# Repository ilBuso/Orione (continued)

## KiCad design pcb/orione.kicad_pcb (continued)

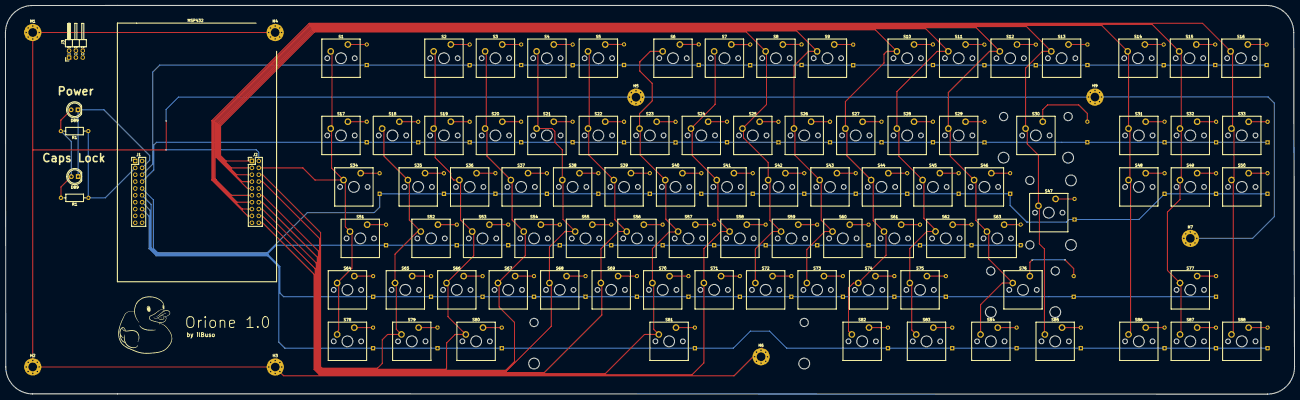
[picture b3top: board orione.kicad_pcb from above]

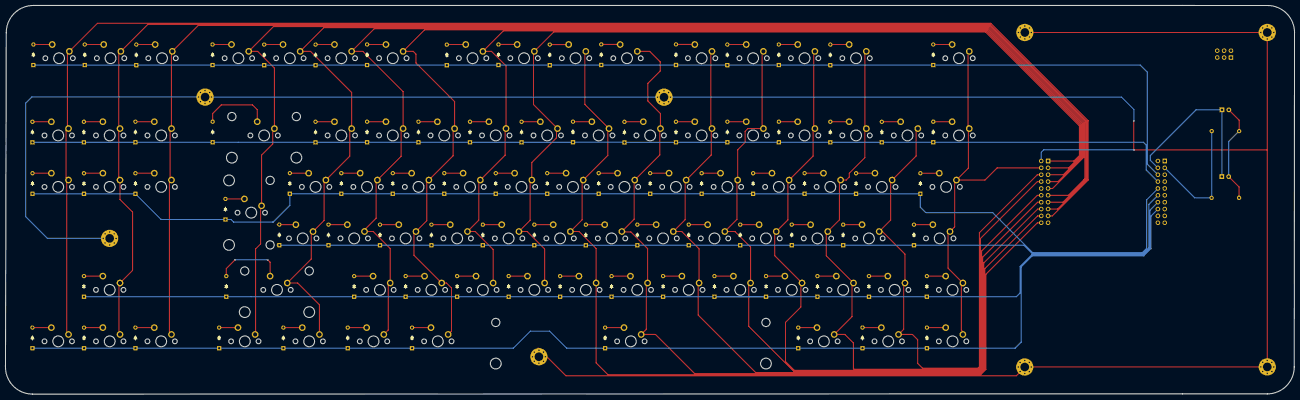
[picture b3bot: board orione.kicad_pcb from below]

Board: 2 copper layers, 477.1 x 143.8 mm, 191 parts (88 on the bottom side), 115 nets.

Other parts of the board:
D89#2: LED; LED_D5.0mm
R1#2: Resistor; R_Axial_DIN0207_L6.3mm_D2.5mm_P10.16mm_Horizontal

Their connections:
GND 1: D89#2.1 (K); also elsewhere on the board
Led 1: R1#2.1; also elsewhere on the board
unnamed 108: D89#2.2 (A), R1#2.2; also elsewhere on the board

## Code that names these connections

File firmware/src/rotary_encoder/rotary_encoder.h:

/**
 * @file rotary_encoder.h
 * @brief Rotary encoder definitions and state structure
 * 
 * Pin definitions, debounce timing constants, and state structure for
 * KY-040 rotary encoder module with integrated push button.
 */

#ifndef ROTARY_ENCODER_H
#define ROTARY_ENCODER_H

    #include <stdint.h>
    #include <stdbool.h>
    
    #include "pico/stdlib.h"
    #include "hardware/sync.h"
    
    #define ROTARY_CLK 19    // CLK pin (A)
    #define ROTARY_DT 20     // DT pin (B)
    #define ROTARY_SW 21     // Switch pin (button)

    // Rotary encoder state
    typedef struct {
        volatile int8_t direction;     // -1 for CCW, 1 for CW, 0 for no change
        volatile bool button_pressed;   // true when button is pressed
        volatile bool has_event;        // true when there's a new event to process
    } rotary_encoder_state_t;

    extern uint32_t last_encoder_time;
    extern uint32_t last_button_time;
    extern uint8_t last_clk_state;
    extern rotary_encoder_state_t rotary_state;

    // Get current state (call from main loop)
    void rotary_encoder_get_state(int8_t* direction, bool* button_pressed);

#endif /* ROTARY_ENCODER_H */

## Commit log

2024-12-30 Updated .gitignore
2024-12-30 Added version 1.0 of the pcb
2024-12-31 minor updtaes to pcb
2024-12-31 Updated MATERIALS.md
2025-01-01 TODO.md
2025-01-02 new usb
2025-01-02 pcv v1
2025-01-02 pcv v1.1
2025-01-03 fixed GND
2025-01-03 fixed power trace
2025-01-05 firmware
2025-01-08 added hw for voltage divider
2025-01-08 added basic sw steps and info for development
2025-01-08 added voltage divider
2025-01-08 added some uart sw steps
2025-01-08 added pin assignment sheet
2025-01-08 changed pin layout of uart
2025-01-08 initialization of ports
2025-01-08 format
2025-01-14 added links to material and uploaded the datasheets
2025-01-15 Changed some Parts
2025-01-15 modified pcb based on new parts
2025-01-15 remove RTS CTS from usb pins because of no use
2025-01-15 remove RTS CTS
2025-01-16 added matrix loop
2025-01-17 Minor refactoring
2025-01-18 Updated firmware
2025-01-18 Orione
2025-01-20 implemented UART comunication
2025-02-25 updated material
2025-03-03 added Rotary Encoder and OLED Display
2025-03-03 added to pcb rotary encoder and oled dysplay
2025-03-03 Updated TODO.md
2025-03-04 refactor repo + updated INFO.md and TODO.md
2025-03-10 interrupt-based implementation
2025-03-10 fixed spelling mistake
2025-03-10 removed interrupt note
2025-03-10 un-commented power-saving mode
2025-03-10 comments
2025-03-16 feat: mac & windows base
2025-03-18 Implementazione Caps Lock
2025-03-18 feat: add interrupt on high to low
2025-03-18 added bug
2025-03-18 possible fix interrupt cicle
2025-03-18 fix: enable interrupt on scan_row
2025-03-19 driver basics
2025-03-19 chore: readme documentation
2025-03-21 added draft for all install scripts
2025-03-21 added draft for all start scripts
2025-03-21 added draft for all driver scripts
2025-03-21 added draft fot the rotary encoder
2025-03-23 Mechanical Debouncing implementation in the firmware
2025-03-24 message code
2025-03-24 message code + refactor of sructure
2025-03-24 feat: on_press and on_release handler for buttons
2025-03-24 fix: removed break on scan_rows()
2025-03-25 fix: now it sends only one signal (or almost) each time the button is pressed
2025-03-25 fix: delete unnecessary code
2025-03-28 updated linux driver
2025-03-28 updated structures
2025-03-28 added basic matrix for othre os
2025-03-30 message system
2025-03-31 minor fixes
2025-04-02 fixes after merge
2025-04-05 markdown update
2025-04-08 toml parsing
2025-04-16 feat: hashmap
2025-04-16 feat: set
2025-04-16 feat: rate limiter implementation
2025-04-16 feat: basic profile switch detection
2025-04-16 some thing
2025-04-16 docs: todos
2025-04-22 fix: now interrupt are working! but only for the current configuration.
2025-04-30 fix: send release signal when the button is not pressed anymore
2025-05-02 Last modifies to the rotary encoder
2025-05-08 commit this I almost lost everything yes this commit message is awful
2025-05-08 lots of stuff
2025-05-09 fixed some bugs
2025-05-09 fixed main
2025-05-19 some things
2025-05-19 helper functions
2025-05-24 prova
2025-05-28 should work
2025-06-04 feat: timer for release button
2025-06-04 feat: add timer for the interupt release
2025-06-04 feat: release event handling
2025-06-04 feat: release event for a single key
2025-06-04 fix: some errors resolved
2025-06-04 fix: bugs
2025-06-04 fixes
2025-06-18 fix: cmakelists file platform bug, build script and other minor bugs
2025-06-18 debug: logs and build scripts
2025-10-05 added RPi pico datashett + updated README.md
2025-10-07 documentation
2025-11-18 bug fix chaged debounce
2025-11-18 fixed documentation
2025-11-20 added presentation
2025-11-20 updated presentation
2025-12-05 updated chassis image
2025-12-07 idk what this code was anymore
2025-12-08 chassis 3D files
2025-12-09 updated fn_keymap
2025-12-09 fixed gosting rotary encoder
2025-12-09 fixed consume buttons
2025-12-09 fixed quick pres on same column
2025-12-09 fixed rotary encoder button
2025-12-11 Update video link in README
2025-12-11 minor fix
